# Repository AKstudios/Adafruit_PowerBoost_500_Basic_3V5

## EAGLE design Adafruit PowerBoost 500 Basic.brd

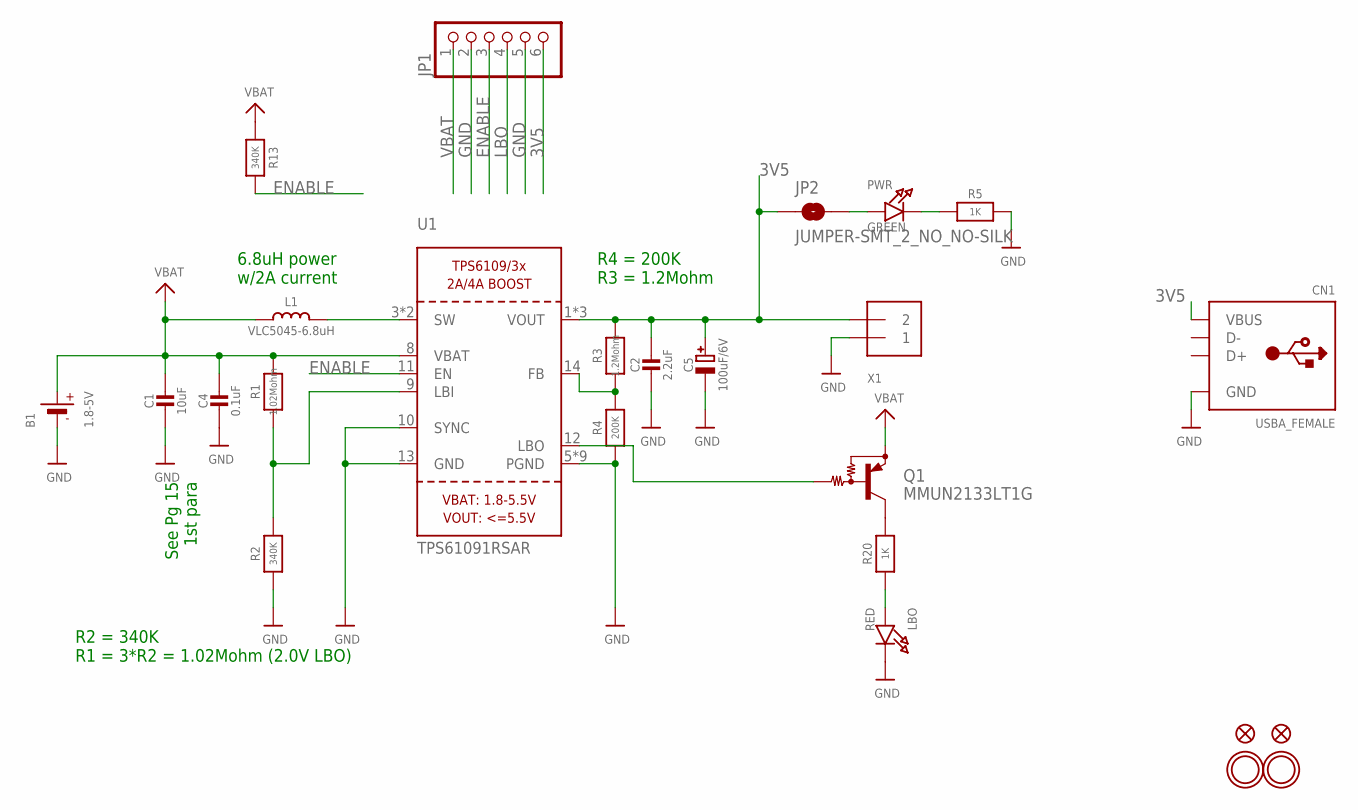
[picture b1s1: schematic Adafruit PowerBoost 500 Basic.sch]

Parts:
B1: 1.8-5V; JSTPH2
C1: 10uF; 0805-NO
C2: 2.2uF; 0805-NO
C4: 0.1uF; 0805-NO
C5: 100uF/6V; EIA3528-21/B-R
CN1: USBA_FEMALE; USB_HOST-PTH
FID2, FID3: FIDUCIAL""; FIDUCIAL_1MM
JP1: PINHD-1X6CB; 1X06-CLEANBIG
JP2: JUMPER-SMT_2_NO_NO-SILK; SMT-JUMPER_2_NO_NO-SILK
L1: VLC5045-6.8uH; INDUCTOR_5X5MM_TDK_VLC5045
LBO: RED; CHIPLED_0805_NOOUTLINE
PWR: GREEN; CHIPLED_0805_NOOUTLINE
Q1: MMUN2133LT1G; SC59-BEC
R1: 1.02Mohm; 0805-NO
R2, R13: 340K; 0805-NO
R3: 1.2Mohm; 0805-NO
R4: 200K; 0805-NO
R5, R20: 1K; 0805-NO
U1: TPS61091RSAR; PVQFN-16
U$10, U$12: MOUNTINGHOLE2.5; MOUNTINGHOLE_2.5_PLATED
X1: TERMBLOCK_1X2; TERMBLOCK_1X2-3.5MM

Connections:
3V5: C2.1, C5.+, CN1.VBUS, JP1.6, JP2.1, R3.2, U1.1 (VOUT), U1.15 (VOUT), U1.16 (VOUT), X1.2
ENABLE: JP1.3, R13.2, U1.11 (EN)
GND: B1.1 (-), C1.2, C2.2, C4.2, C5.-, CN1.GND, JP1.2, JP1.5, LBO.C, R2.1, R4.1, R5.2, U1.5 (PGND), U1.6 (PGND), U1.7 (PGND), U1.10 (SYNC), U1.13 (GND), U1.P$18 (PGND), U1.P$19 (PGND), U1.P$20 (PGND), U1.P$21 (PGND), U1.P$22 (PGND), U1.THERMAL (PGND), X1.1
LBO: JP1.4, Q1.B, U1.12 (LBO)
unnamed: L1.P$2 (2), U1.3 (SW), U1.4 (SW)
unnamed: LBO.A, R20.1
unnamed: R1.1, R2.2, U1.9 (LBI)
unnamed: PWR.C, R5.1
unnamed: R3.1, R4.2, U1.14 (FB)
unnamed: JP2.2, PWR.A
unnamed: Q1.C, R20.2
VBAT: B1.2 (+), C1.1, C4.1, JP1.1, L1.P$1 (1), Q1.E, R1.2, R13.1, U1.8 (VBAT)

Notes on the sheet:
See Pg 15 1st para
6.8uH power w/2A current
R2 = 340K R1 = 3*R2 = 1.02Mohm (2.0V LBO)
R4 = 200K R3 = 1.2Mohm

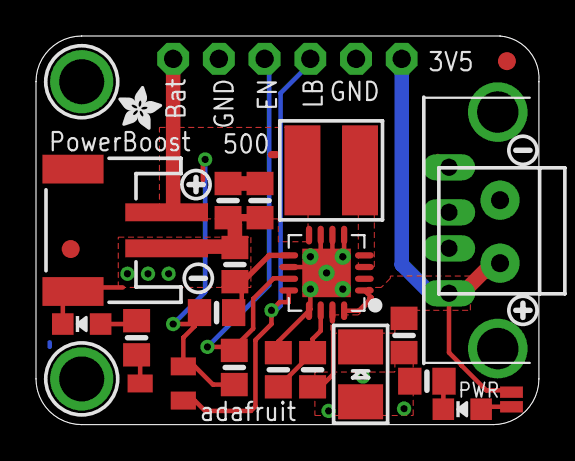
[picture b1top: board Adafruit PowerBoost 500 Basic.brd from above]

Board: 2 copper layers, 27.9 x 21.6 mm, 31 parts (1 on the bottom side), 12 nets.

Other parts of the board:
U$13, U$25: SYMBOL_PLUS
U$23, U$26: SYMBOL_MINUS
U$28: ADAFRUIT_2.5MM
U$29: ADAFRUIT_5MM

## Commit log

2017-06-04 :circus_tent: Added .gitattributes & .gitignore files
2017-06-04 Init

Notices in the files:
parts and their libraries:
microbuilder: This work is placed in the public domain, and may be freely used for commercial and non-commercial work with the following conditions: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
SparkFun-Jumpers: Licensing: Creative Commons ShareAlike 4.0 International - https://creativecommons.org/licenses/by-sa/4.0
